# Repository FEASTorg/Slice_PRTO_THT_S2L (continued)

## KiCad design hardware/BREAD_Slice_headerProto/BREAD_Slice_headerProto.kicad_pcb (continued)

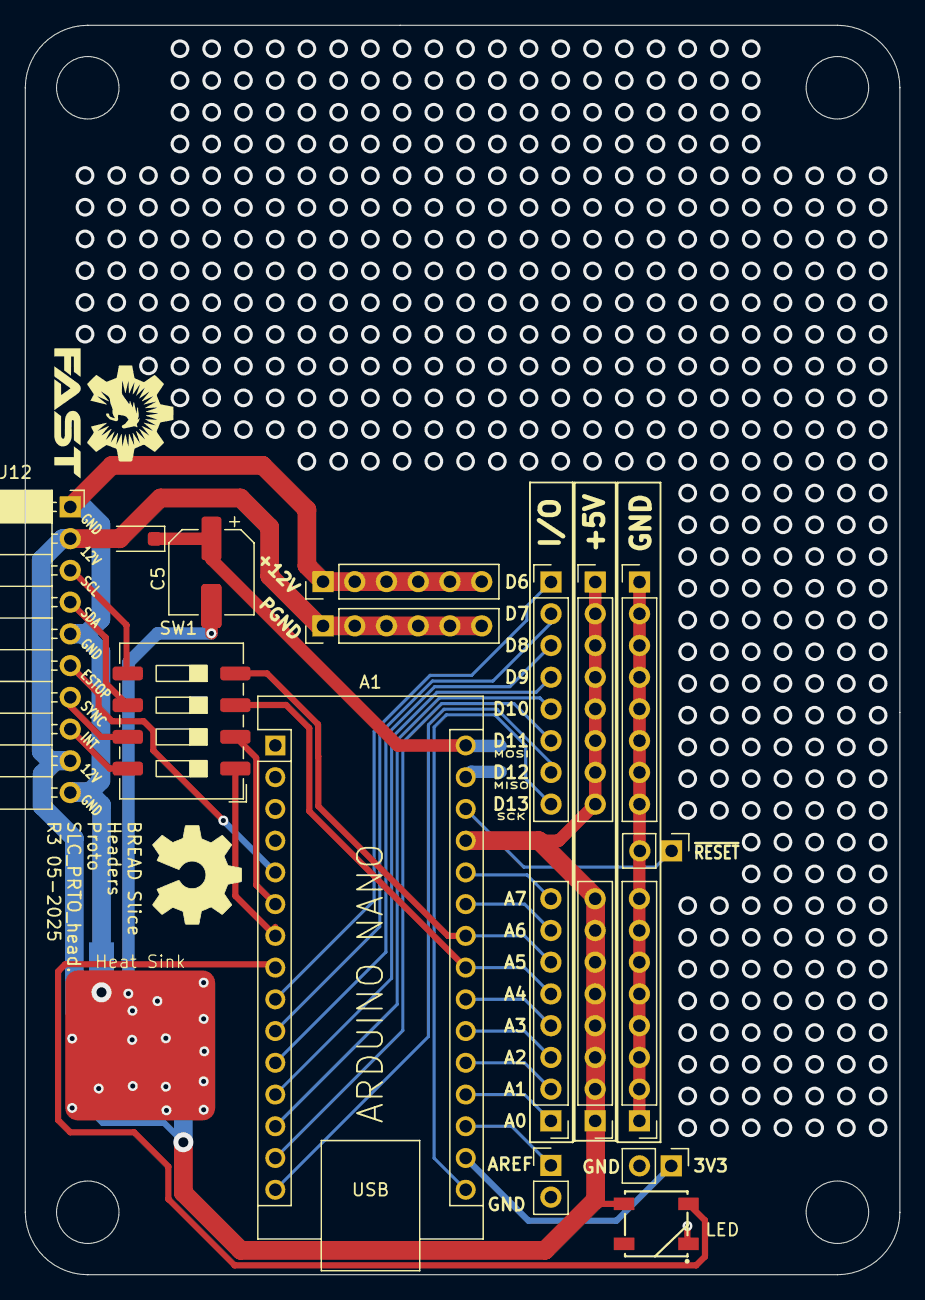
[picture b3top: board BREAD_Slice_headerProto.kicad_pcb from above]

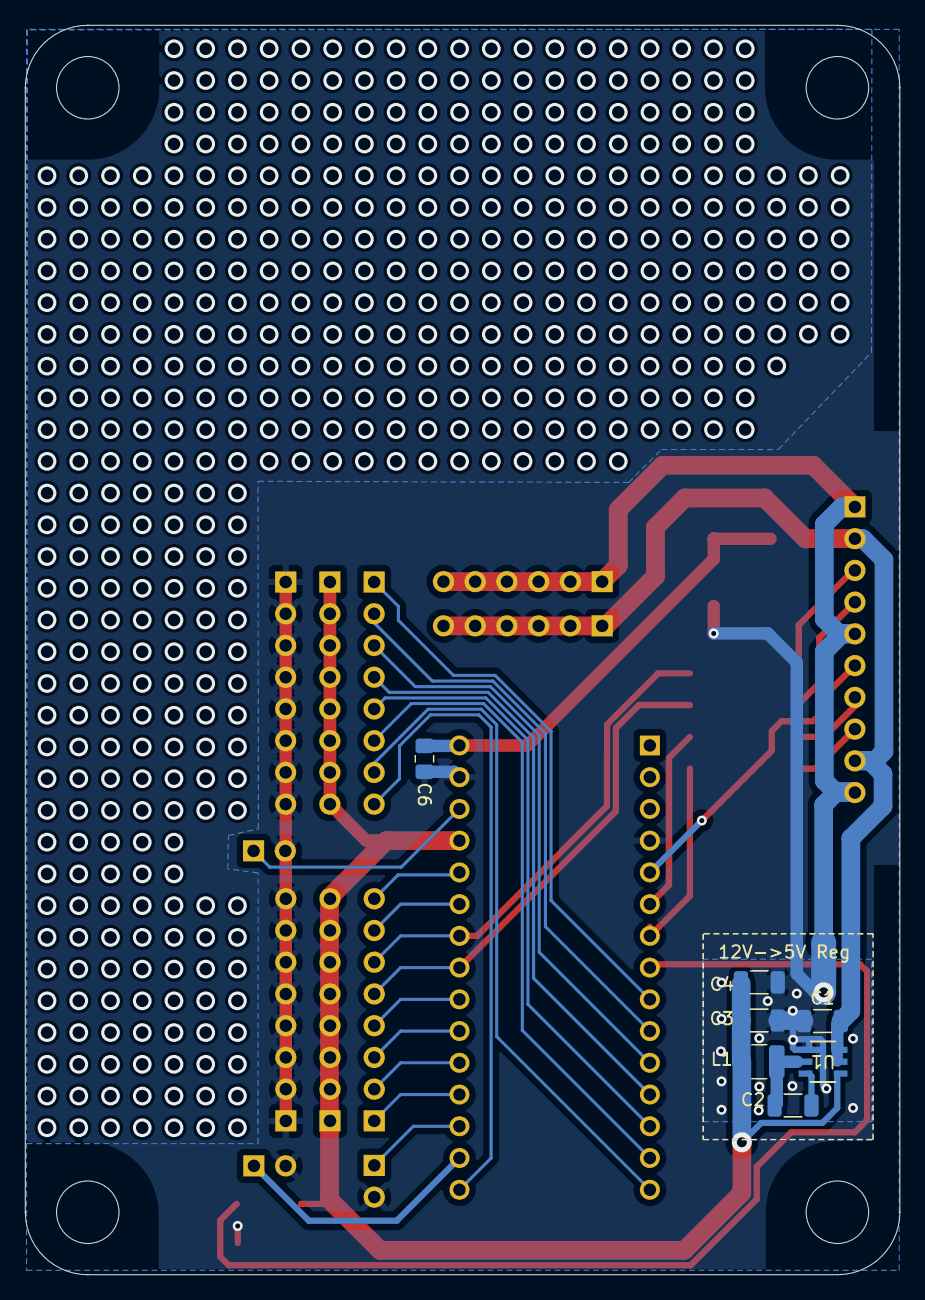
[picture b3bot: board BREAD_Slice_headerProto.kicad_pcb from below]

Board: 2 copper layers, 70.0 x 100.0 mm, 31 parts (8 on the bottom side), 34 nets.

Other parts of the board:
Ref**: Val**; OSHW_Logo_8mm

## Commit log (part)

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2025-04-02 initial commit breaking off from Slice_TEMP
2025-04-19 minor tweaks
2025-05-04 added header proto variant to test new temp
2025-05-07 generated outputs to order
2025-09-24 initial commit after split
2025-09-24 clear erc and drc but this board needs some rebuild help long term
2025-09-24 ci: initial commit with bread-infra workflow
2025-09-24 📄 KiBot index + board renders (auto)
2026-01-26 review and revise board and update footprints
2026-04-20 refactor: org casing rename from 'FEASTorg' to 'feastorg'
2026-05-20 Add slice.yaml manifest (schema v1.0)
2026-05-24 Add standardized TODO.md with Pass 1/Pass 2 structure
